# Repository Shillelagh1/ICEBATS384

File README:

**ICE Boards are All The Same.**

> [!CAUTION]
> This project is a heavy work in progress in it's early stages.
> It would be greatly appreciated if you could review and provide feedback on my schematic,
> but it's heavily advised you don't attempt to build this board yet.

# Summary:
This board is designed as a small universal FPGA daughterboard that can be added to any project without having to construct a unique layout for each project. It features a 40 pin mezzanine connector to attach to the parent board which offers access to all of the FPGA IO, Clock Hardware Controls, FPGA Configuration controls, and flash programming.

# Hardware:
+ Lattice ICE40LP384-SG32 FPGA.
+ Winbond W25X40C 4MBit Flash.
+ 16MHz Application configurable FPGA Clock.
+ Configuration done and Power OK status LEDs.
+ 2 User program controlled status LEDs.
+ 2mm Clearance daughterboard mezzanine connector.

> [!IMPORTANT]
> Because of the intended small form factor of this board it may be difficult to manufacture for some.

# TODO:
- [X] Rough board layout.
- [ ] Large scale prototype board.
- [ ] Final schematic review.
- [ ] First revision prototype assembled.
- [ ] Prototype rework (Or it works first try?)
- [ ] All features test.
- [ ] Project integration.

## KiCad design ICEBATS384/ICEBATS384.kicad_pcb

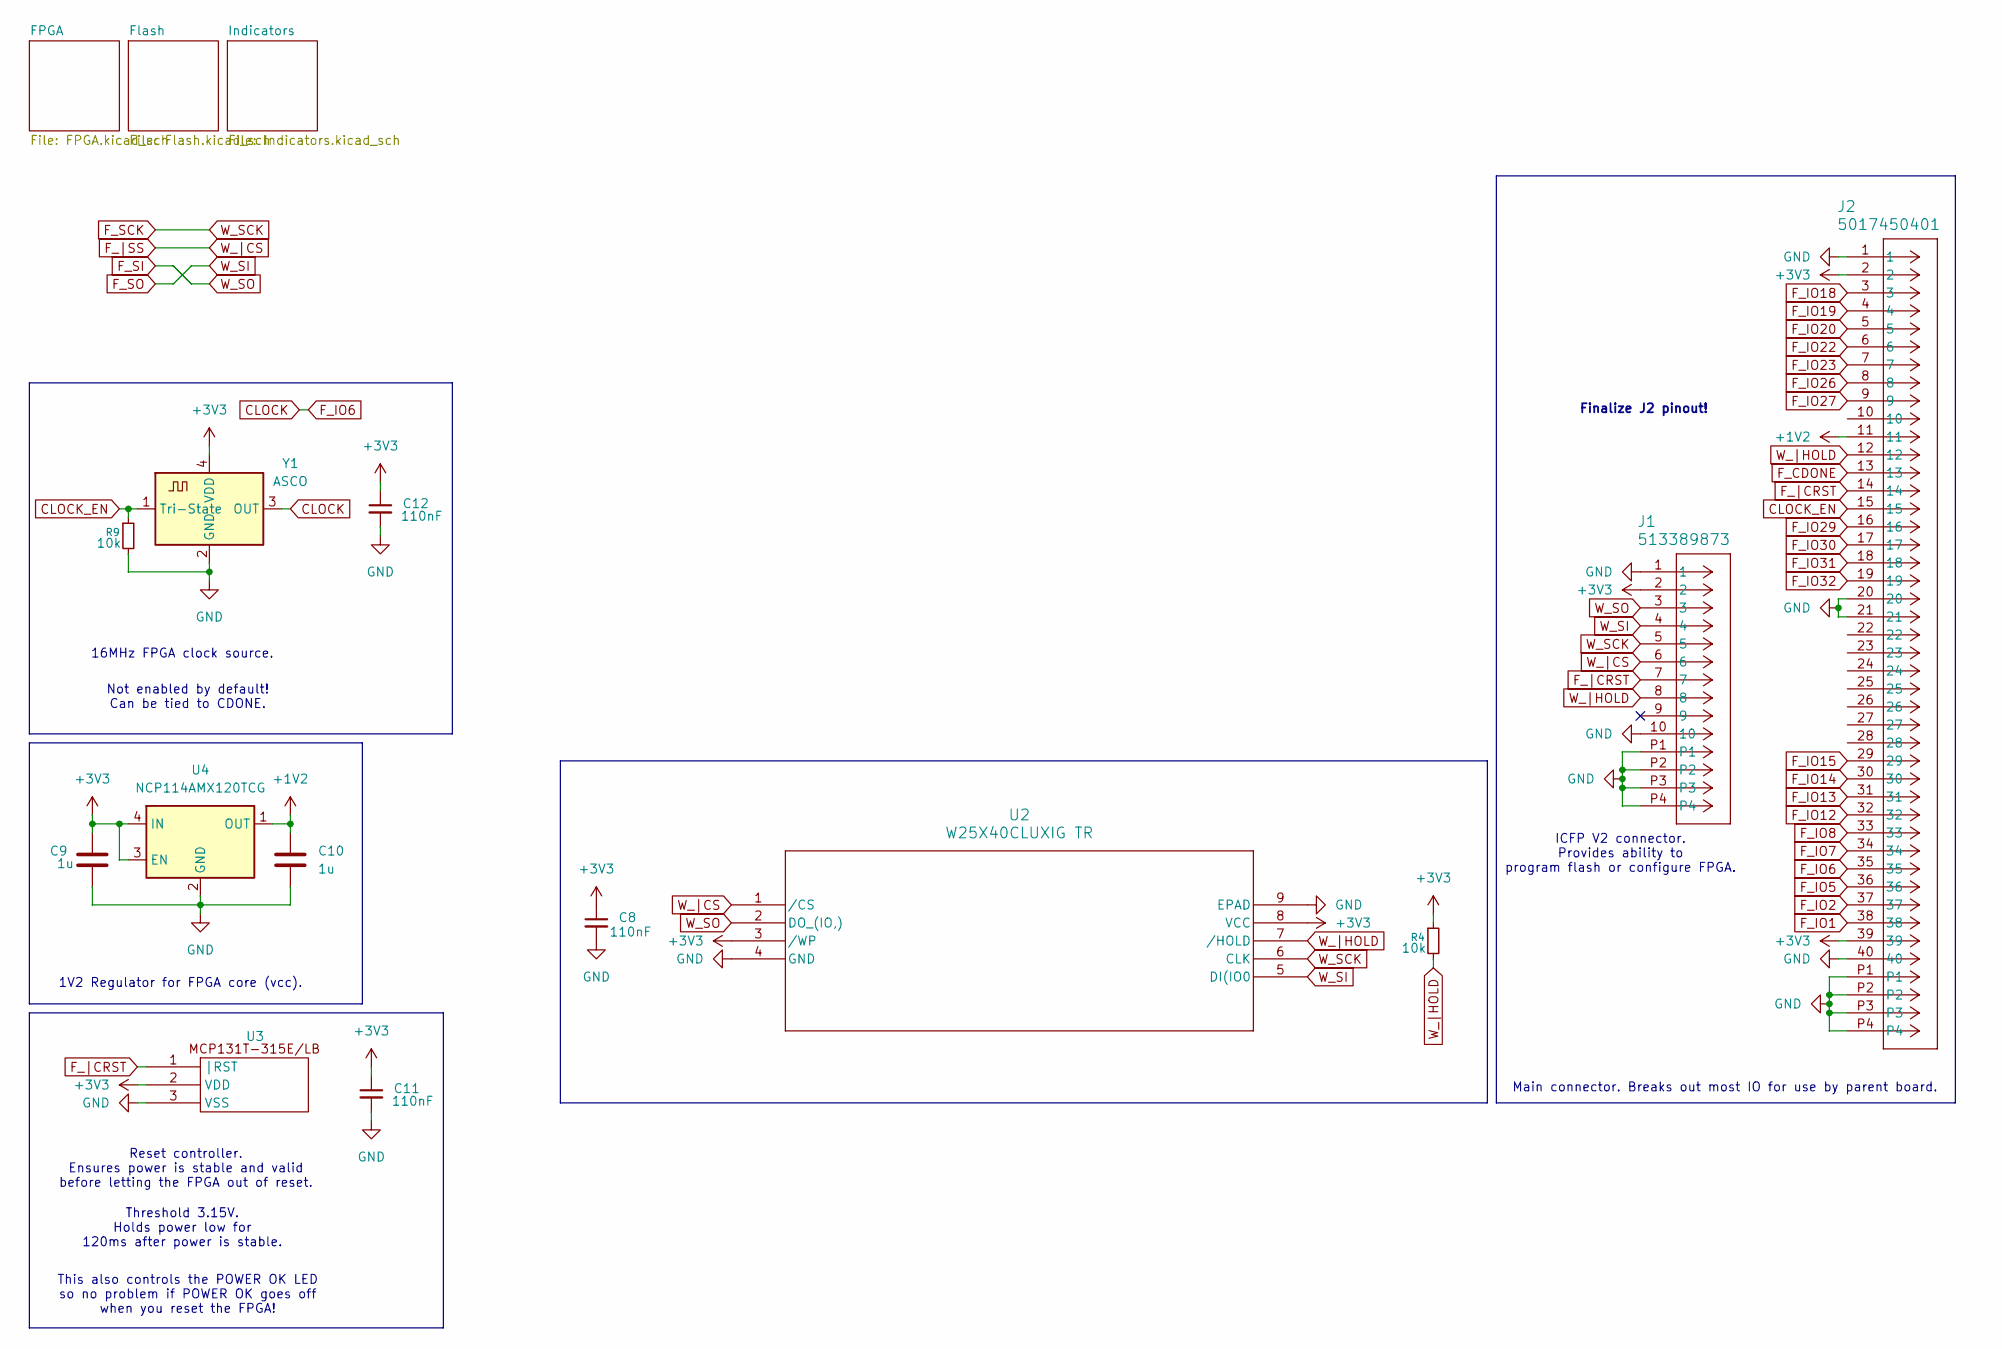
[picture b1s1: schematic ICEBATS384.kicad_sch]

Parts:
C8, C11, C12: 110nF; C_0402_1005Metric
C9, C10: 1u; C_0603_1608Metric
J1: 513389873; CON_513389873
J2: 5017450401; CON_5017450401
R4, R9: 10k; R_0402_1005Metric
U2: W25X40CLUXIG TR; Winbond_USON-8-1EP_3x2mm_P0.5mm_EP0.2x1.6mm
U3: SOT-323_SC-70
U4: NCP114AMX120TCG; OnSemi_XDFN4-1EP_1.0x1.0mm_EP0.52x0.52mm
Y1: ASCO; Oscillator_SMD_Abracon_ASE-4Pin_3.2x2.5mm

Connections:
+1V2: C10.1, J2.11, U4.1 (OUT); also elsewhere on the board
+3V3: C8.1, C9.1, C11.1, C12.1, J1.2, J2.2, J2.39, R4.1, U2.3 (/WP), U2.8 (VCC), U3.2 (VDD), U4.3 (EN), U4.4 (IN), Y1.4 (VDD); also elsewhere on the board
CLOCK: J2.35, Y1.3 (OUT); also elsewhere on the board
CLOCK_EN: J2.15, R9.1, Y1.1 (Tri-State)
F_CDONE: J2.13; also elsewhere on the board
F_IO1: J2.38; also elsewhere on the board
F_IO2: J2.37; also elsewhere on the board
F_IO5: J2.36; also elsewhere on the board
F_IO7: J2.34; also elsewhere on the board
F_IO8: J2.33; also elsewhere on the board
F_IO12: J1.4, J2.32, U2.5 (DI(IO0); also elsewhere on the board
F_IO13: J1.3, J2.31, U2.2 (DO_(IO,)); also elsewhere on the board
F_IO14: J1.6, J2.30, U2.1 (/CS); also elsewhere on the board
F_IO15: J1.5, J2.29, U2.6 (CLK); also elsewhere on the board
F_IO18: J2.3; also elsewhere on the board
F_IO19: J2.4; also elsewhere on the board
F_IO20: J2.5; also elsewhere on the board
F_IO22: J2.6; also elsewhere on the board
F_IO23: J2.7; also elsewhere on the board
F_IO26: J2.8; also elsewhere on the board
F_IO27: J2.9; also elsewhere on the board
F_IO29: J2.16; also elsewhere on the board
F_IO30: J2.17; also elsewhere on the board
F_IO31: J2.18; also elsewhere on the board
F_IO32: J2.19; also elsewhere on the board
F_|CRST: J1.7, J2.14, U3.1 (|RST); also elsewhere on the board
GND: C8.2, C9.2, C10.2, C11.2, C12.2, J1.1, J1.10, J1.P1, J1.P2, J1.P3, J1.P4, J2.1, J2.20, J2.21, J2.40, J2.P1, J2.P2, J2.P3, J2.P4, R9.2, U2.4 (GND), U2.9 (EPAD), U3.3 (VSS), U4.2 (GND), U4.5 (GND), Y1.2 (GND); also elsewhere on the board
W_|HOLD: J1.8, J2.12, R4.2, U2.7 (/HOLD)

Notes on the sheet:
Main connector. Breaks out most IO for use by parent board.
16MHz FPGA clock source.
Reset controller. Ensures power is stable and valid before letting the FPGA out of reset.
This also controls the POWER OK LED so no problem if POWER OK goes off when you reset the FPGA!
1V2 Regulator for FPGA core (vcc).
Threshold 3.15V. Holds power low for 120ms after power is stable.
ICFP V2 connector. Provides ability to program flash or configure FPGA.
Finalize J2 pinout!
Not enabled by default! Can be tied to CDONE.

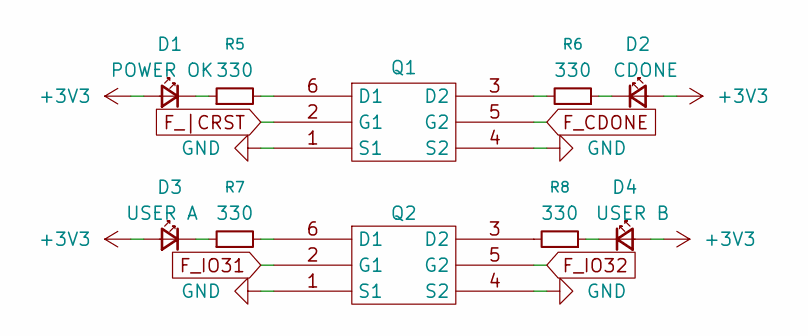
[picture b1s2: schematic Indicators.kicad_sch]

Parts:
D1: POWER OK; D_0402_1005Metric
D2: CDONE; D_0402_1005Metric
D3: USER A; D_0402_1005Metric
D4: USER B; D_0402_1005Metric
Q1, Q2: DFN-6-1EP_2x2mm_P0.65mm_EP1.01x1.7mm
R5, R6, R7, R8: 330; R_0402_1005Metric

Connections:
+3V3: D1.2 (A), D2.2 (A), D3.2 (A), D4.2 (A); also elsewhere on the board
F_CDONE: Q1.5 (G2); also elsewhere on the board
F_IO31: Q2.2 (G1); also elsewhere on the board
F_IO32: Q2.5 (G2); also elsewhere on the board
F_|CRST: Q1.2 (G1); also elsewhere on the board
GND: Q1.1 (S1), Q1.4 (S2), Q1.7, Q2.1 (S1), Q2.4 (S2), Q2.7; also elsewhere on the board
unnamed: D1.1 (K), R5.1
unnamed: D2.1 (K), R6.1
unnamed: D3.1 (K), R7.1
unnamed: D4.1 (K), R8.1
unnamed: Q1.6 (D1), R5.2
unnamed: Q1.3 (D2), R6.2
unnamed: Q2.6 (D1), R7.2
unnamed: Q2.3 (D2), R8.2

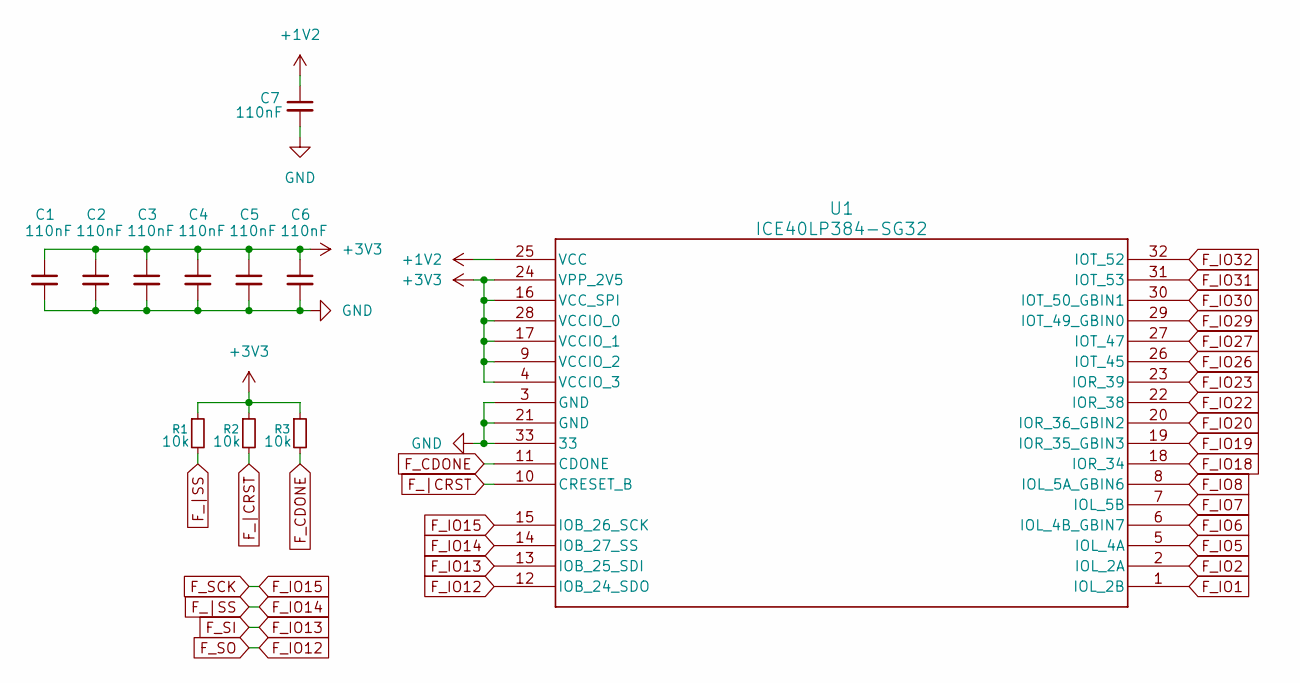
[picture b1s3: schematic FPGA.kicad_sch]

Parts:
C1, C2, C3, C4, C5, C6, C7: 110nF; C_0402_1005Metric
R1, R2, R3: 10k; R_0402_1005Metric
U1: ICE40LP384-SG32; QFN-32-1EP_5x5mm_P0.5mm_EP3.1x3.1mm

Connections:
+1V2: C7.1, U1.25 (VCC); also elsewhere on the board
+3V3: C1.1, C2.1, C3.1, C4.1, C5.1, C6.1, R1.1, R2.1, R3.1, U1.4 (VCCIO_3), U1.9 (VCCIO_2), U1.16 (VCC_SPI), U1.17 (VCCIO_1), U1.24 (VPP_2V5), U1.28 (VCCIO_0); also elsewhere on the board
CLOCK: U1.6 (IOL_4B_GBIN7); also elsewhere on the board
F_CDONE: R3.2, U1.11 (CDONE); also elsewhere on the board
F_IO1: U1.1 (IOL_2B); also elsewhere on the board
F_IO2: U1.2 (IOL_2A); also elsewhere on the board
F_IO5: U1.5 (IOL_4A); also elsewhere on the board
F_IO7: U1.7 (IOL_5B); also elsewhere on the board
F_IO8: U1.8 (IOL_5A_GBIN6); also elsewhere on the board
F_IO12: U1.12 (IOB_24_SDO); also elsewhere on the board
F_IO13: U1.13 (IOB_25_SDI); also elsewhere on the board
F_IO14: R1.2, U1.14 (IOB_27_SS); also elsewhere on the board
F_IO15: U1.15 (IOB_26_SCK); also elsewhere on the board
F_IO18: U1.18 (IOR_34); also elsewhere on the board
F_IO19: U1.19 (IOR_35_GBIN3); also elsewhere on the board
F_IO20: U1.20 (IOR_36_GBIN2); also elsewhere on the board
F_IO22: U1.22 (IOR_38); also elsewhere on the board
F_IO23: U1.23 (IOR_39); also elsewhere on the board
F_IO26: U1.26 (IOT_45); also elsewhere on the board
F_IO27: U1.27 (IOT_47); also elsewhere on the board
F_IO29: U1.29 (IOT_49_GBIN0); also elsewhere on the board
F_IO30: U1.30 (IOT_50_GBIN1); also elsewhere on the board
F_IO31: U1.31 (IOT_53); also elsewhere on the board
F_IO32: U1.32 (IOT_52); also elsewhere on the board
F_|CRST: R2.2, U1.10 (CRESET_B); also elsewhere on the board
GND: C1.2, C2.2, C3.2, C4.2, C5.2, C6.2, C7.2, U1.3 (GND), U1.21 (GND), U1.33; also elsewhere on the board

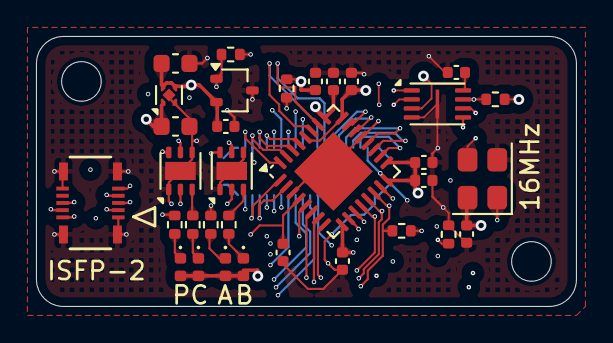
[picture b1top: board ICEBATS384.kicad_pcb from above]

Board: 4 copper layers, 30.0 x 15.0 mm, 34 parts (1 on the bottom side), 36 nets.

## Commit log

2025-06-13 Init
2025-06-13 Fixes missing schematic connections.
2025-06-13 Fixes board rear silkscreen
2025-06-13 Documentation
2025-06-13 Documentation, License
2025-06-13 Sheet documentation
2025-06-14 README
2025-06-14 Schematics
